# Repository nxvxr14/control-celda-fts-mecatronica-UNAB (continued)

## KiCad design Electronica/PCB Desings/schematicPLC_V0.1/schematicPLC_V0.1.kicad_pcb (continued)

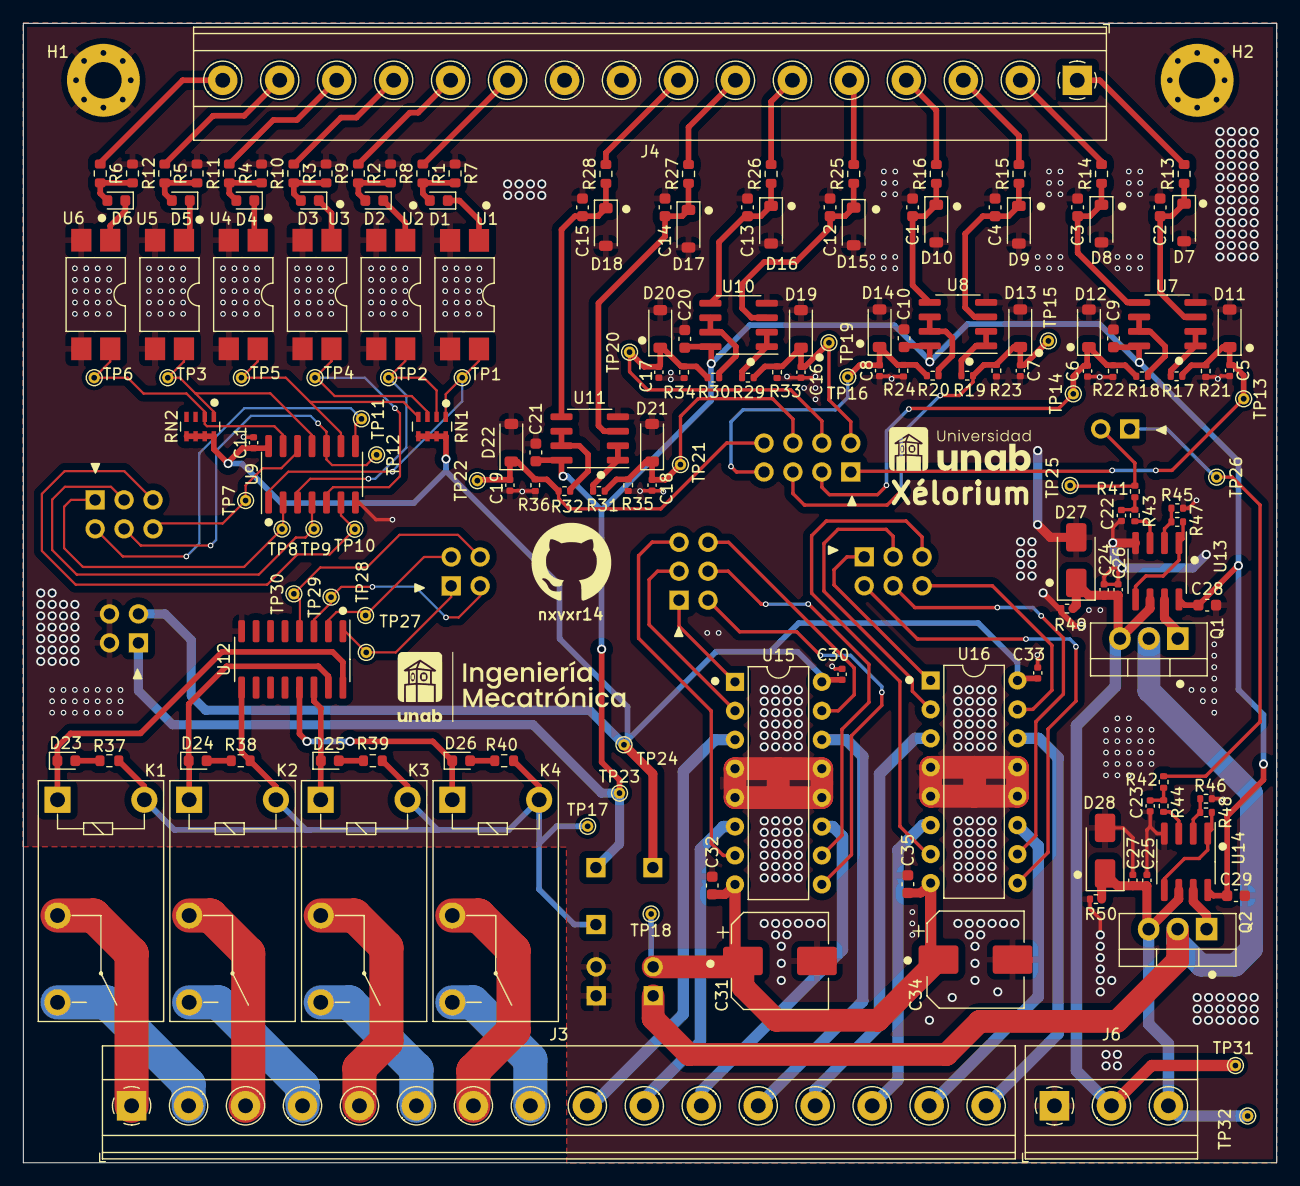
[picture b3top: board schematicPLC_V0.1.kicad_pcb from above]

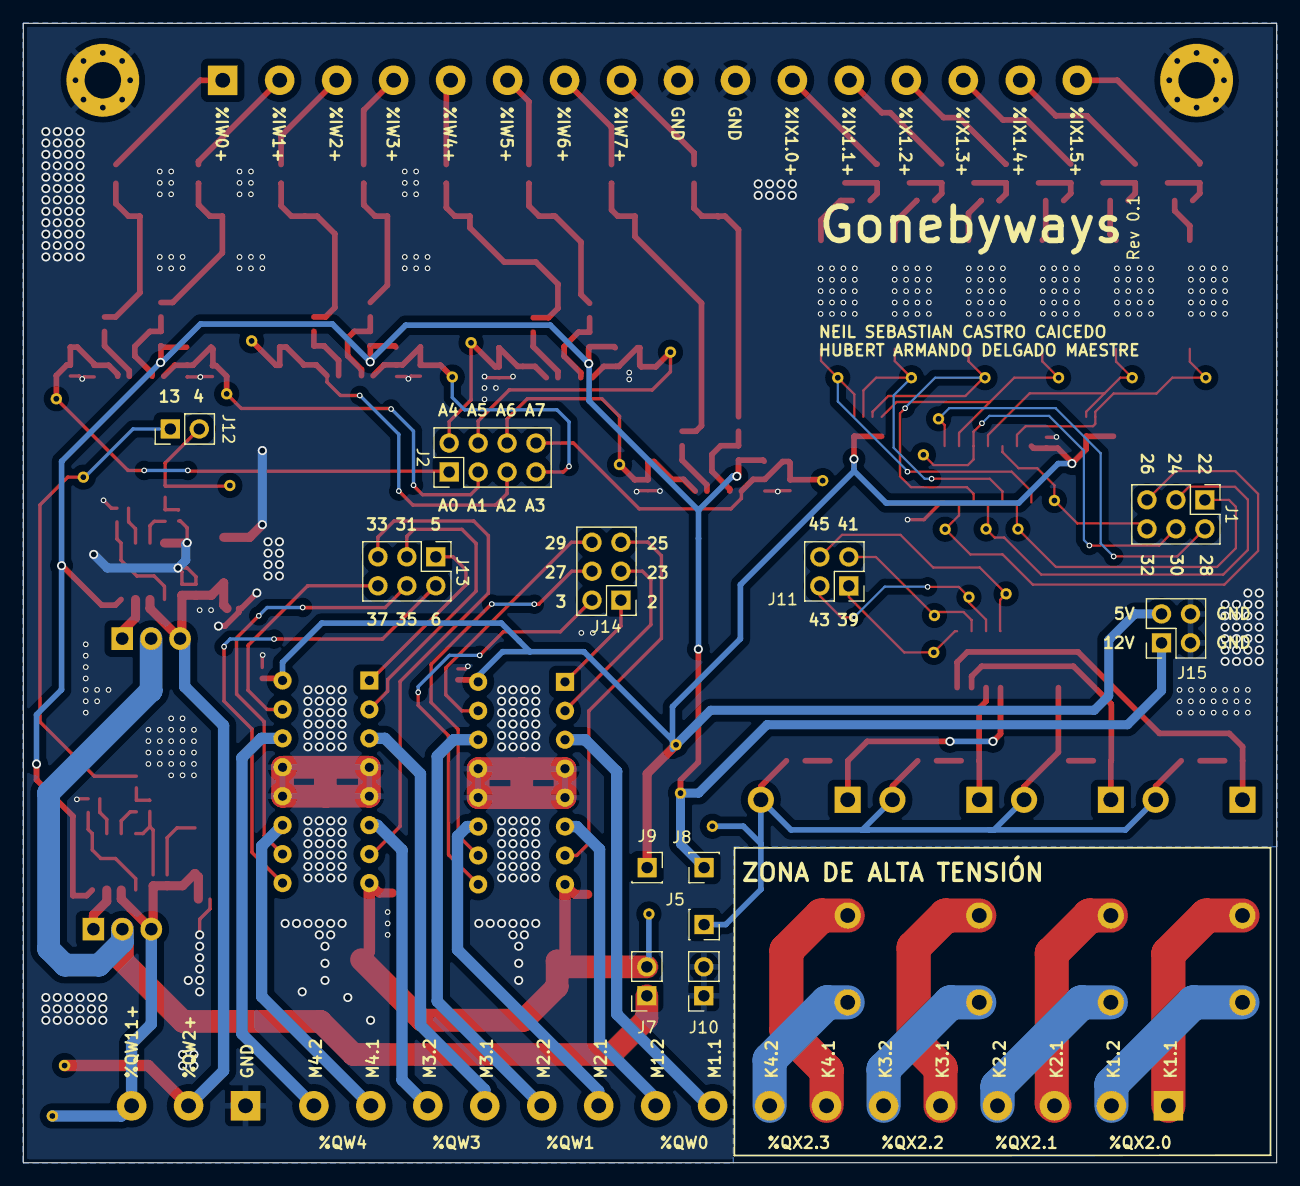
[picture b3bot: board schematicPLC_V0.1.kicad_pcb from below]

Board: 2 copper layers, 110.0 x 100.0 mm, 186 parts (12 on the bottom side), 121 nets.

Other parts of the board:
J15: voltageSourceInput_Conn_02x02_Odd_Even; PinHeader_2x02_P2.54mm_Vertical

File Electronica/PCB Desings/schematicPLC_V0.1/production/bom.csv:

Designator,Footprint,Quantity,Value,LCSC Part #
"C1, C10, C12, C13, C14, C15, C2, C20, C21, C28, C29, C3, C32, C35, C4, C9",0603,16,C0603/100nF/50V,C14663
"C11, C16, C17, C18, C19, C24, C25, C30, C33, C5, C6, C7, C8",0402,13,C0402/100nF/16V,C1525
"C22, C23, C26, C27",0402,4,C0402/1uF/25V,C52923
"C31, C34",CP_Elec_8x10,2,CD8xL10/220uF/25V,C178279
D1,0603,1,LED0603/RED/X0,C2286
"D10, D15, D16, D17, D18, D7, D8, D9",D_SOD-123,8,SOD123/MMSZ5240BT1G/10V,C82084
"D11, D12, D13, D14, D19, D20, D21, D22",D_SOD-123,8,SOD123/MMSZ5231B-7-F/5.1V,C85181
D2,0603,1,LED0603/RED/X1,C2286
D23,0603,1,LED0603/YELLOW/K1,C72038
D24,0603,1,LED0603/YELLOW/K2,C72038
D25,0603,1,LED0603/YELLOW/K3,C72038
D26,0603,1,LED0603/YELLOW/K4,C72038
"D27, D28",D_SMA,2,SMD/M7(1N4007),C95872
D3,0603,1,LED0603/RED/X2,C2286
D4,0603,1,LED0603/RED/X3,C2286
D5,0603,1,LED0603/RED/X4,C2286
D6,0603,1,LED0603/RED/X5,C2286
"H1, H2",MountingHole_3.2mm_M3_Pad_Via,2,MH 3.2mm M3,
J1,PinHeader_2x03_P2.54mm_Vertical,1,digitalInputToMega_Conn_02x03_Odd_Even,
J10,PinSocket_1x02_P2.54mm_Vertical,1,GND_Conn_01x02,
J11,PinHeader_2x02_P2.54mm_Vertical,1,digitalOutputFromMega_Conn_02x02_Odd_Even,
J12,PinHeader_1x02_P2.54mm_Vertical,1,analogInputFromMega_Conn_01x02,
"J13, J14",PinHeader_2x03_P2.54mm_Vertical,2,MotorOutputFromMega_Conn_02x03_Odd_Even,
J15,PinHeader_2x02_P2.54mm_Vertical,1,voltageSourceInput_Conn_02x02_Odd_Even,
J2,PinHeader_2x04_P2.54mm_Vertical,1,analogInputToMega_Conn_02x04_Odd_Even,
J3,"TerminalBlock_Phoenix_MKDS-1,5-16_1x16_P5.00mm_Horizontal",1,outputs_Screw_Terminal_01x16,
J4,"TerminalBlock_Phoenix_MKDS-1,5-16_1x16_P5.00mm_Horizontal",1,inputs_Screw_Terminal_01x16,
J5,PinSocket_1x01_P2.54mm_Vertical,1,24Vin_Conn_01x01,
J6,"TerminalBlock_Phoenix_MKDS-1,5-3_1x03_P5.00mm_Horizontal",1,outputs_Screw_Terminal_01x03,
J7,PinSocket_1x02_P2.54mm_Vertical,1,10Vin_Conn_01x02,
J8,PinSocket_1x01_P2.54mm_Vertical,1,12Vin_Conn_01x01,
J9,PinSocket_1x01_P2.54mm_Vertical,1,5Vin_Conn_01x01,
"K1, K2, K3, K4",Relay_SPST_Omron-G5Q-1A,4,G5Q-1A4 DC24,C89311
"Q1, Q2",TO-220-3_Vertical,2,TIP31C,C963401
"R1, R13, R14, R15, R16, R2, R25, R26, R27, R28, R3, R37, R38, R39, R4, R40, R5, R6",0603,18,R0603/2K2,C4190
"R10, R11, R12, R7, R8, R9",0603,6,R0603/560R,C23204
"R17, R18, R19, R20, R21, R22, R23, R24, R29, R30, R31, R32, R33, R34, R35, R36, R49, R50",0402,18,R0402/1K,C11702
"R41, R42, R43, R44",0402,4,R0402/47K,C25792
"R45, R46, R47, R48",0402,4,R0402/20K,C25765
"RN1, RN2",R_Array_Concave_4x0603,2,R0603X4/10K,C29718
TP1,TestPoint_THTPad_D1.0mm_Drill0.5mm,1,TP_XG0,
TP10,TestPoint_THTPad_D1.0mm_Drill0.5mm,1,TP_X2,
TP11,TestPoint_THTPad_D1.0mm_Drill0.5mm,1,TP_X3,
TP12,TestPoint_THTPad_D1.0mm_Drill0.5mm,1,TP_X4,
TP13,TestPoint_THTPad_D1.0mm_Drill0.5mm,1,TP_ADC0,
TP14,TestPoint_THTPad_D1.0mm_Drill0.5mm,1,TP_ADC1,
TP15,TestPoint_THTPad_D1.0mm_Drill0.5mm,1,TP_ADC2,
TP16,TestPoint_THTPad_D1.0mm_Drill0.5mm,1,TP_ADC3,
TP17,TestPoint_THTPad_D1.0mm_Drill0.5mm,1,TP_24V,
TP18,TestPoint_THTPad_D1.0mm_Drill0.5mm,1,TP_10V,
TP19,TestPoint_THTPad_D1.0mm_Drill0.5mm,1,TP_ADC4,
TP2,TestPoint_THTPad_D1.0mm_Drill0.5mm,1,TP_XG1,
TP20,TestPoint_THTPad_D1.0mm_Drill0.5mm,1,TP_ADC5,
TP21,TestPoint_THTPad_D1.0mm_Drill0.5mm,1,TP_ADC6,
TP22,TestPoint_THTPad_D1.0mm_Drill0.5mm,1,TP_ADC7,
TP23,TestPoint_THTPad_D1.0mm_Drill0.5mm,1,TP_12V,
TP24,TestPoint_THTPad_D1.0mm_Drill0.5mm,1,TP_5V,
TP25,TestPoint_THTPad_D1.0mm_Drill0.5mm,1,TP_PWM1,
TP26,TestPoint_THTPad_D1.0mm_Drill0.5mm,1,TP_PWM2,
TP27,TestPoint_THTPad_D1.0mm_Drill0.5mm,1,TP_Q1,
TP28,TestPoint_THTPad_D1.0mm_Drill0.5mm,1,TP_Q2,
TP29,TestPoint_THTPad_D1.0mm_Drill0.5mm,1,TP_Q3,
TP3,TestPoint_THTPad_D1.0mm_Drill0.5mm,1,TP_XG4,
TP30,TestPoint_THTPad_D1.0mm_Drill0.5mm,1,TP_Q4,
TP31,TestPoint_THTPad_D1.0mm_Drill0.5mm,1,TP_010_1,
TP32,TestPoint_THTPad_D1.0mm_Drill0.5mm,1,TP_010_2,
TP4,TestPoint_THTPad_D1.0mm_Drill0.5mm,1,TP_XG2,
TP5,TestPoint_THTPad_D1.0mm_Drill0.5mm,1,TP_XG3,
TP6,TestPoint_THTPad_D1.0mm_Drill0.5mm,1,TP_XG5,
TP7,TestPoint_THTPad_D1.0mm_Drill0.5mm,1,TP_X5,
TP8,TestPoint_THTPad_D1.0mm_Drill0.5mm,1,TP_X0,
TP9,TestPoint_THTPad_D1.0mm_Drill0.5mm,1,TP_X1,
"U1, U2, U3, U4, U5, U6",SMDIP-4_W9.53mm,6,SMD-4P/EL817S1(C)(TU)-F,C106900
"U10, U11, U13, U14, U7, U8",SOIC-8_3.9x4.9mm_P1.27mm,6,SOIC8/LM358,C7950
U12,SOIC-16_3.9x9.9mm_P1.27mm,1,SOIC-16/ULN2003A,C7512
"U15, U16",DIP-16_W7.62mm,2,L293D/DIP-16,C12340
U9,SOIC-14_3.9x8.7mm_P1.27mm,1,SOIC-14/74HC14,C5605

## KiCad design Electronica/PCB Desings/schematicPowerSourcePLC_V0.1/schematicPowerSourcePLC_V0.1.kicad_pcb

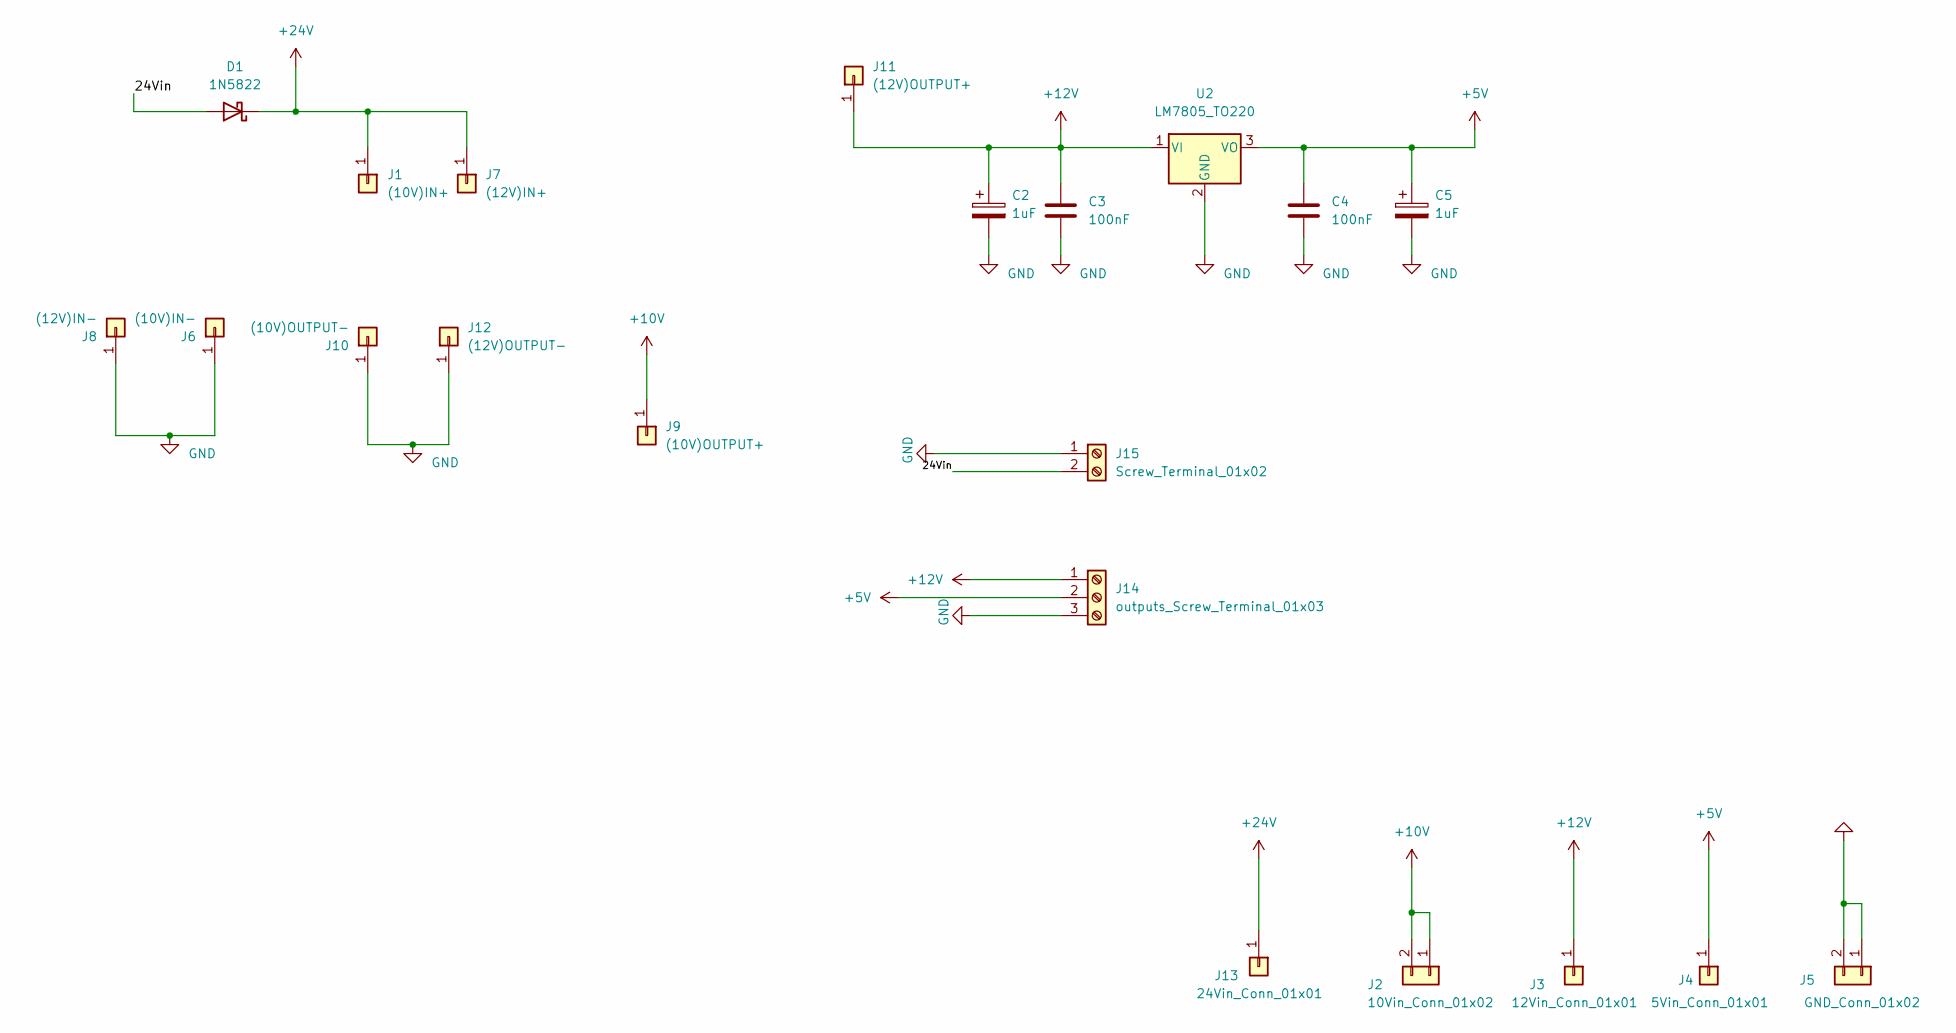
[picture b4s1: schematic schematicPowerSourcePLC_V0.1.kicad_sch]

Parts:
C2, C5: 1uF; CP_Radial_D5.0mm_P2.00mm
C3, C4: 100nF; C_Disc_D4.3mm_W1.9mm_P5.00mm
D1: 1N5822; D_DO-41_SOD81_P12.70mm_Horizontal
J1: (10V)IN+; PinHeader_1x01_P2.54mm_Vertical
J2: 10Vin_Conn_01x02; PinHeader_1x02_P2.54mm_Vertical
J3: 12Vin_Conn_01x01; PinHeader_1x01_P2.54mm_Vertical
J4: 5Vin_Conn_01x01; PinHeader_1x01_P2.54mm_Vertical
J5: GND_Conn_01x02; PinHeader_1x02_P2.54mm_Vertical
J6: (10V)IN-; PinHeader_1x01_P2.54mm_Vertical
J7: (12V)IN+; PinHeader_1x01_P2.54mm_Vertical
J8: (12V)IN-; PinHeader_1x01_P2.54mm_Vertical
J9: (10V)OUTPUT+; PinHeader_1x01_P2.54mm_Vertical
J10: (10V)OUTPUT-; PinHeader_1x01_P2.54mm_Vertical
J11: (12V)OUTPUT+; PinHeader_1x01_P2.54mm_Vertical
J12: (12V)OUTPUT-; PinHeader_1x01_P2.54mm_Vertical
J13: 24Vin_Conn_01x01; PinHeader_1x01_P2.54mm_Vertical
J14: outputs_Screw_Terminal_01x03; TerminalBlock_Phoenix_MKDS-1,5-3_1x03_P5.00mm_Horizontal
J15: Screw_Terminal_01x02; TerminalBlock_Phoenix_MKDS-1,5-2_1x02_P5.00mm_Horizontal
U2: LM7805_TO220; TO-220-3_Vertical

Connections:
+5V: C4.1, C5.1, J4.1, J14.2, U2.3 (VO)
+10V: J2.1, J2.2, J9.1
+12V: C2.1, C3.1, J3.1, J11.1, J14.1, U2.1 (VI)
+24V: D1.1 (K), J1.1, J7.1, J13.1
/24Vin: D1.2 (A), J15.2
GND: C2.2, C3.2, C4.2, C5.2, J5.1, J5.2, J6.1, J8.1, J10.1, J12.1, J14.3, J15.1, U2.2 (GND)

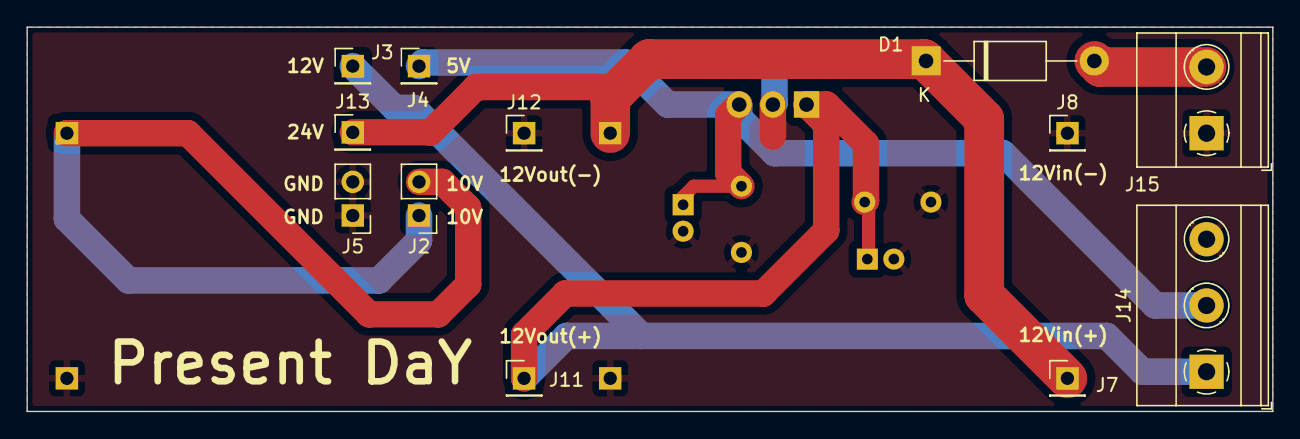
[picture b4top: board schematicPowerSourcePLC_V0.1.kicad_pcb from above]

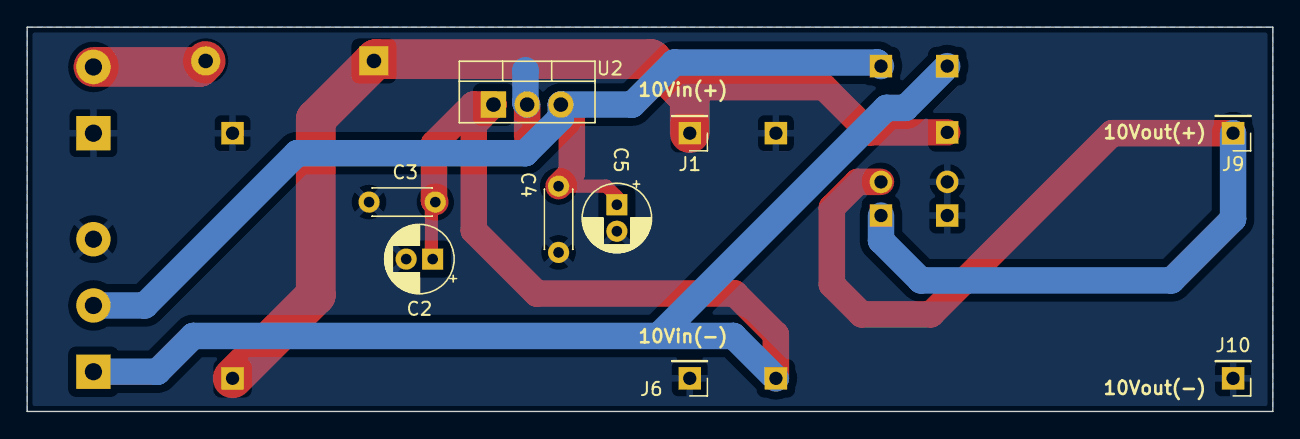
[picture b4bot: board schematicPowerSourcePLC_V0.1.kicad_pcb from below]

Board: 2 copper layers, 94.0 x 29.0 mm, 21 parts (9 on the bottom side), 6 nets.

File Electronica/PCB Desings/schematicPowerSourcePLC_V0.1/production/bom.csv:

Designator,Footprint,Quantity,Value,LCSC Part #
"C2, C5",CP_Radial_D5.0mm_P2.00mm,2,1uF,
"C3, C4",C_Disc_D4.3mm_W1.9mm_P5.00mm,2,100nF,
D1,D_DO-41_SOD81_P12.70mm_Horizontal,1,1N5822,
J1,PinHeader_1x01_P2.54mm_Vertical,1,(10V)IN+,
J10,PinHeader_1x01_P2.54mm_Vertical,1,(10V)OUTPUT-,
J11,PinHeader_1x01_P2.54mm_Vertical,1,(12V)OUTPUT+,
J12,PinHeader_1x01_P2.54mm_Vertical,1,(12V)OUTPUT-,
J13,PinHeader_1x01_P2.54mm_Vertical,1,24Vin_Conn_01x01,
J14,"TerminalBlock_Phoenix_MKDS-1,5-3_1x03_P5.00mm_Horizontal",1,outputs_Screw_Terminal_01x03,
J15,"TerminalBlock_Phoenix_MKDS-1,5-2_1x02_P5.00mm_Horizontal",1,Screw_Terminal_01x02,
J2,PinHeader_1x02_P2.54mm_Vertical,1,10Vin_Conn_01x02,
J3,PinHeader_1x01_P2.54mm_Vertical,1,12Vin_Conn_01x01,
J4,PinHeader_1x01_P2.54mm_Vertical,1,5Vin_Conn_01x01,
J5,PinHeader_1x02_P2.54mm_Vertical,1,GND_Conn_01x02,
J6,PinHeader_1x01_P2.54mm_Vertical,1,(10V)IN-,
J7,PinHeader_1x01_P2.54mm_Vertical,1,(12V)IN+,
J8,PinHeader_1x01_P2.54mm_Vertical,1,(12V)IN-,
J9,PinHeader_1x01_P2.54mm_Vertical,1,(10V)OUTPUT+,
U2,TO-220-3_Vertical,1,LM7805_TO220,

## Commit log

2025-11-10 Video
